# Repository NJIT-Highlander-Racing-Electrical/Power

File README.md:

# Power

A repository dedicated to everything power-related: batteries, connectors, wiring, battery management, systems, and more.

## Batteries

* Zippy 5000mAh 11.1v batteries
  * Can be ran in parallel after balancing for extra capacity
  * Housed in a 3D printed dual battery holder
  * Two thumb screws lock the batteries into place with a cover bar
* Battery Management System
  * Uses a Low Voltage Disconnect Module to cut off battery power when battery voltage gets too low
  * Ideally includes short circuit protection or fuse

## Wiring

* 14 AWG wire for main power bus connections
* 24 AWG wire to split off to smaller subsystems 
* CAN-Bus signals are sent over 24 AWG twisted pair wire
* All subsystems use 4-pin Aviation Plug Connectors for 12V power and CAN-Bus signals

## Voltage Regulation at Subsystems

* All subsystems will have a 5V switching regulators
   * Running the vehicle power bus at 12V but each subsystem only requiring 5V allows for a voltage drop on the bus without issues
   * Switching regulators are far more efficient than linear regulators, which would get too hot stepping down from 12V to 5V at higher loads
   * The ESP32 can also output 3.3V from the 5V we supply if needed for its subsystems

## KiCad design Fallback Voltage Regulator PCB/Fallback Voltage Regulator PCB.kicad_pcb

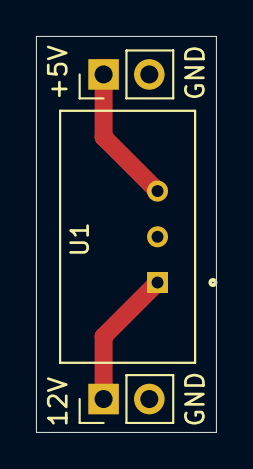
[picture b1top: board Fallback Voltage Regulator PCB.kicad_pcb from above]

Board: 2 copper layers, 10.0 x 22.0 mm, 3 parts (0 on the bottom side), 3 nets.

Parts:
J1, J2: Conn_01x02; PinHeader_1x02_P2.54mm_Vertical
U1: TR10S05-Voltage-Regulator; TR10S05

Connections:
/+12V: J1.1, U1.1 (VIN)
GND: J1.2, J2.2, U1.2 (GND)
unnamed: J2.1, U1.3 (VOUT)

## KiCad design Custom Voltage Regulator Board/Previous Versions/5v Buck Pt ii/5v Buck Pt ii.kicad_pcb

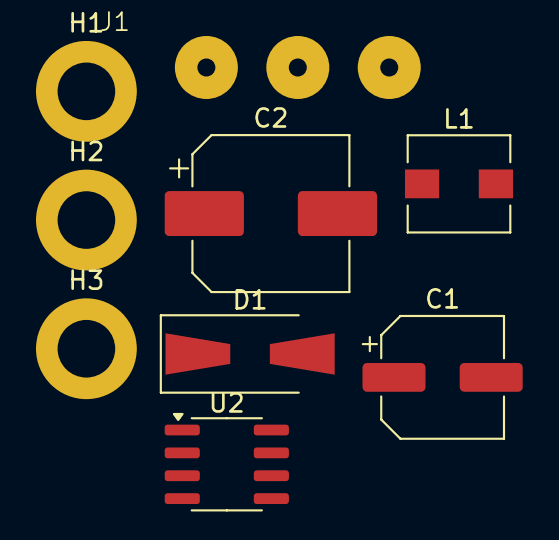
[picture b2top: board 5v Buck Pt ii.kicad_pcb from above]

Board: 2 copper layers, 9 parts (0 on the bottom side), 4 nets, no tracks yet.

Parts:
C1: 100 uF; CP_Elec_6.3x5.4_Nichicon
C2: 1000 uF; CP_Elec_8x10.5
D1: 1N5822; D_SMA-SMB_Universal_Handsoldering
H1, H2, H3: MountingHole_Pad; MountingHole_3.2mm_M3_DIN965_Pad
J1: Conn_01x03_Pin; cast
L1: 100 uH; L_Wuerth_HCI-5040
U2: GL2576-5.0SF8DR; SOIC-8_3.9x4.9mm_P1.27mm

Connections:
+5V: C2.1, H3.1, J1.1, L1.2, U2.3 (FB)
+15V: C1.1, H1.1, J1.3, U2.1 (VIN)
GND: C1.2, C2.2, D1.2 (A), H2.1, J1.2, U2.4 (~ON/OFF), U2.5 (GND), U2.6 (GND), U2.7 (GND), U2.8 (GND)
unnamed: D1.1 (K), L1.1, U2.2 (VOUT)

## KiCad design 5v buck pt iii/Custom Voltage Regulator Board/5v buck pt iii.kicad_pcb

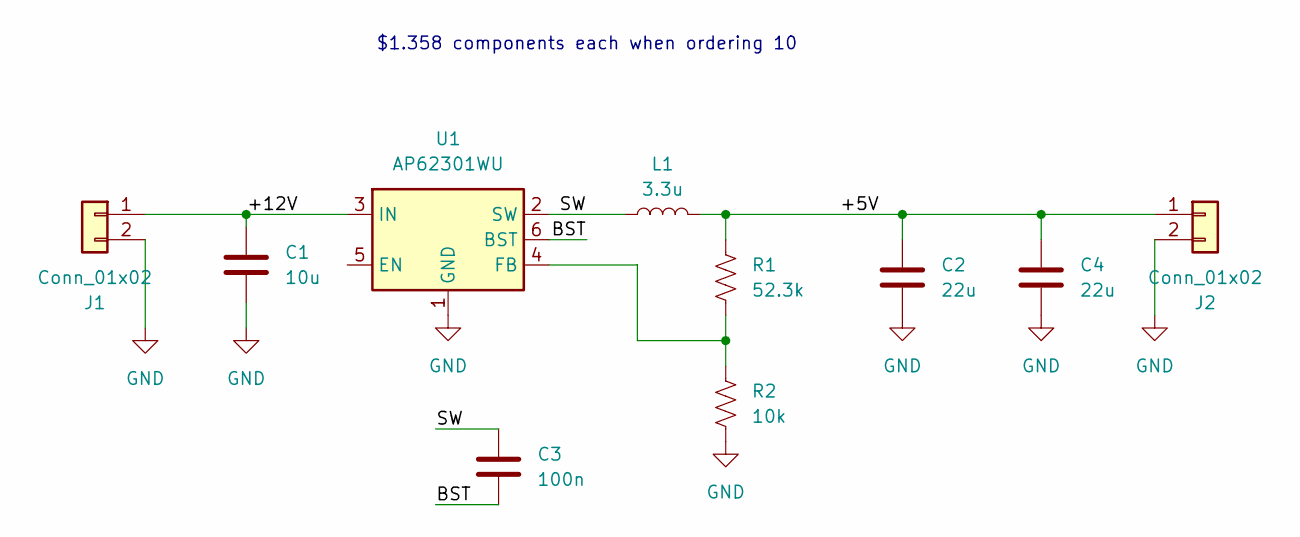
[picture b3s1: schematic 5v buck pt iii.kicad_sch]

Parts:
C1: 10u; C_0603_1608Metric
C2, C4: 22u; C_0603_1608Metric
C3: 100n; C_0402_1005Metric
J1, J2: Conn_01x02; PinHeader_1x02_P2.54mm_Vertical
L1: 3.3u; L_Taiyo-Yuden_NR-50xx
R1: 52.3k; R_0402_1005Metric
R2: 10k; R_0402_1005Metric
U1: AP62301WU; TSOT-23-6

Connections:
/+5V: C2.1, C4.1, J2.1, L1.2, R1.1
/+12V: C1.1, J1.1, U1.3 (IN)
/BST: C3.2, U1.6 (BST)
/SW: C3.1, L1.1, U1.2 (SW)
GND: C1.2, C2.2, C4.2, J1.2, J2.2, R2.2, U1.1 (GND)
unnamed: R1.2, R2.1, U1.4 (FB)

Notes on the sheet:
$1.358 components each when ordering 10

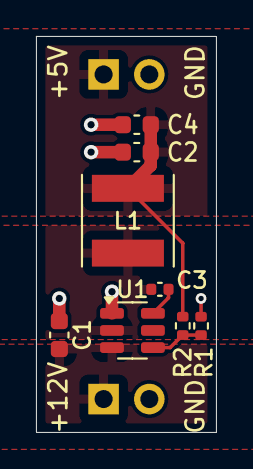
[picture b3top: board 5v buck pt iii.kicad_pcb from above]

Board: 2 copper layers, 10.0 x 22.0 mm, 10 parts (0 on the bottom side), 6 nets.

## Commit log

2024-02-07 Add files via upload
    Rough sketch of wiring in car. Blue squares represent XT60 connectors breaking off of the main power bus. The purpose of these is to allow for us to adjust the length of the wires connecting the subs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
2024-03-13 Create DummyFile
2024-04-17 Rename Battery Holder V2 v22.f3d to Battery-Holder/Battery Holder V2 v22.f3d
2024-04-21 Update and rename Brake Light 9V Battery Clamshell Top Half.step to Brake Light 9V Battery Clamshell Top Half.step.
2024-04-21 organized project files
2024-04-21 Rename IMG_1292.JPG to Photos/IMG_1292.JPG
2024-05-14 moving 2023-2024 files to archive
2024-05-14 adding default files and folders
2024-10-02 Create Components
2024-10-03 Update Components
2024-10-12 add 5v buck part 3
2024-10-17 Rename 5v buck pt iii/5v buck pt iii.kicad_pcb to 5v buck pt iii/Custom Voltage Regulator Board/5v buck pt iii.kicad_pcb
2024-10-17 Rename 5v buck pt iii/Custom Voltage Regulator Board/5v buck pt iii.kicad_pcb to Custom Voltage Regulator Board/5v buck pt iii.kicad_pcb
2024-10-17 Rename 5v buck pt iii.kicad_prl to 5v buck pt iii.kicad_prl
2024-10-17 Rename 5v buck pt iii.kicad_pro to 5v buck pt iii.kicad_pro
2024-10-17 Rename 5v buck pt iii.kicad_sch to 5v buck pt iii.kicad_sch
2024-10-17 Rename fp-info-cache to fp-info-cache
2024-10-17 Organize Files
2024-12-12 Add battery box
2024-12-27 Add fallback voltage regulator board that uses TR10S05 Regulator
2024-12-28 Add GBR and DRL files for fallback pcb
2025-01-05 Update Battery Box Model
2025-01-06 Update 3D Models
